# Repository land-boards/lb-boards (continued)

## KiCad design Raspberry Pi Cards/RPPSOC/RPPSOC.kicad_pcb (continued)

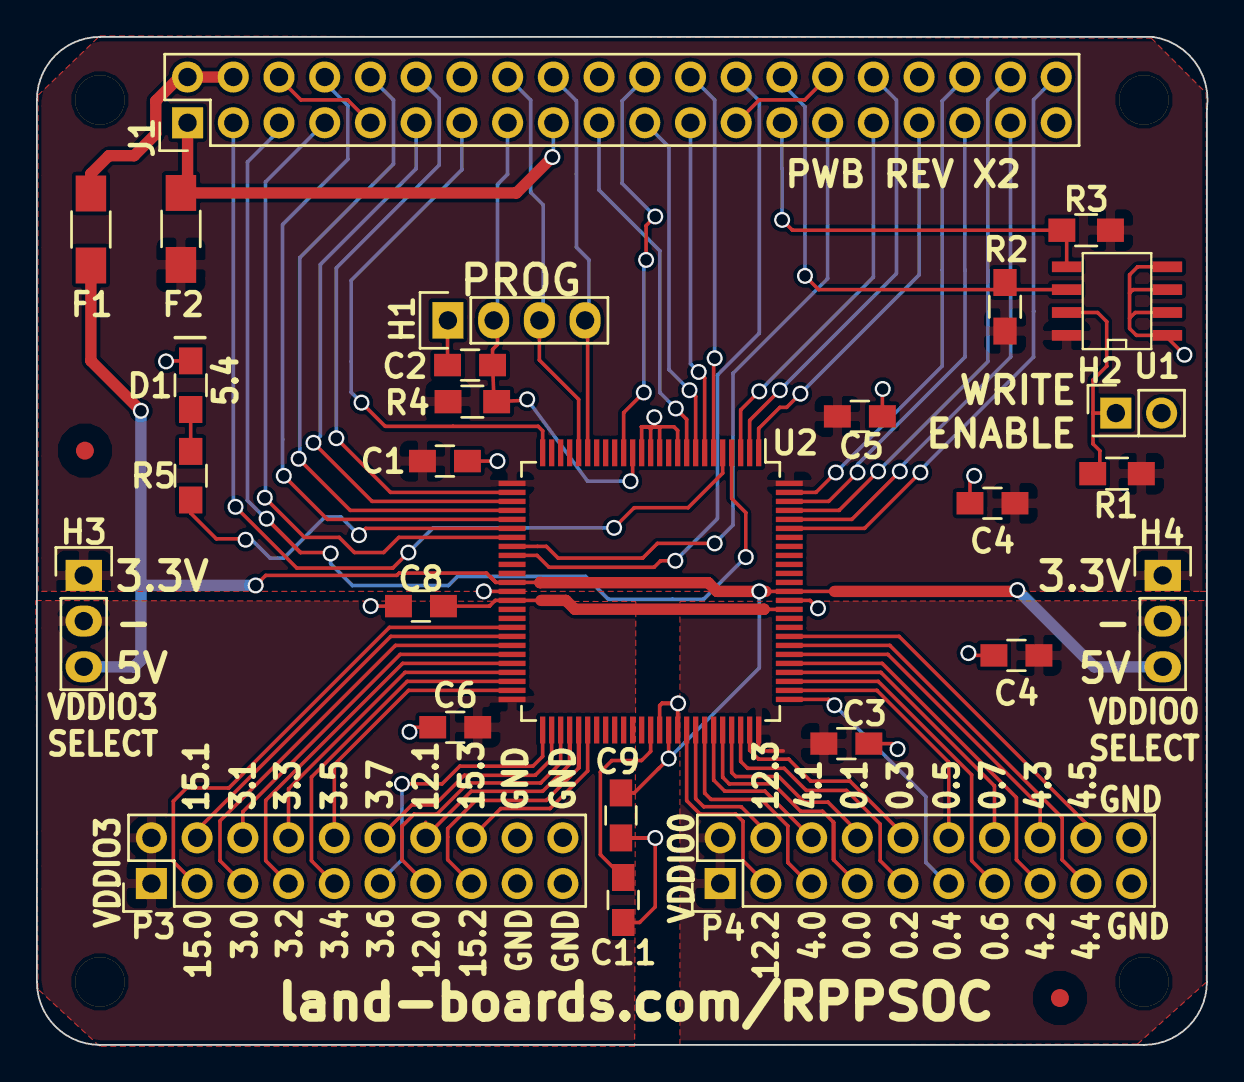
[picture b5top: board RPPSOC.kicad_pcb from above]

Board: 2 copper layers, 65.0 x 56.0 mm, 34 parts (1 on the bottom side), 70 nets.

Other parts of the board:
C4#2: 1uF; C_0805_HandSoldering
TEST: COUPON; REV_BLOCK

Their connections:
/VZ0: C4#2.1; also elsewhere on the board
GND: C4#2.2; also elsewhere on the board
